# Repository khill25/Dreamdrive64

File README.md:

# DREAMDrive64
Nintendo 64 flash cart based around Raspberry Pi RP2040s. Load roms up to 64MB, EEPROM save support, supports all cic versions.

---
# Getting one
## Buy one from my website! 
https://dreamcraftindustries.com/products/dreamdrive64

## Build your own with PCBWay
You can load up the hw files in Kicad and use the PCBWay plugin. The PCBWay plugin will take you right to the PCBWay website with the gerbers loaded up and ready to order. 

### N64 Cartridge Shell
You can use a doner shell or find some on Aliexpress/Ebay.
The shell will need to be cut to accomodate the SD Card slot and USB port.

* SD Card Slot Cuts 
	* These cuts should be 15mm wide
		* This cut should start approximately 46.5mm from the bottom of the shell on the outside edge.
	* 3mm Deep on the back shell
	* Less than 1mm deep on the front shell
	
* "Boot" Button (Press while plugging in USB to load new firmware)
	* Drill small hole
		* 28.6mm from left side of back shell (5mm right of screw hole)
		* ~6.2mm down from the screw hole

---
# Current Dev Status
* DREAMDrive64 can boot roms and has made the v1.0.0 release! 
	* Menu rom can navigate the sd file system assuming a rational number of files/folders (256 at the moment per directory, 10 directory depth limit)
	* Menu rom can render thumbnail boxart of a rom when scrolling through file list
	* Libdragon changes are needed if you want to compile your own rom for the firmware, those changes are in PR over at the libdragon repo
	* Firmware is stable with a v1.0.0 release available right now, with more improvements on the way.

## Features
| Feature					| Status 	 | Notes 	|
|--------------------------:|:-----------|---------:|
| Rom Loading				| Complete!	 |			|
| SD Filesystem navigation	| Complete!	 | Folder/File limit ~100 per directory 		|
| Wifi						| Soon		 |			|
| EEPROM save support		| Complete!		 |			|
| SRAM support 				| Complete!  | Some games require much higher sram timing than is currently working. SRAM doesn't save to SD card. SRAM data will only persist while the game is running.		|
| CIC Compatibility			| Complete!	 | All cic versions should work. Country version however needs to be matched with the version flashed to the board (PAL vs NTSC) |

**ROM Compatibility **
Still working towards booting at full sdk speeds (0x1240) but current v1.0.0 firmware is at 0x2040. SRAM access isn't fast enough for some titles. 

# Command Registers
| Register					| Address 	 | Length 	| Notes 				|
|--------------------------:|:-----------|:---------|----------------------:|
| Base Address				| 0x1FFE0000 | 0x1000	| 4kB buffer/Currently shared as internal buffer   			| v1/lite and v2|
| Command Interface Start	| 0x1FFE1000 | 0x0800	|						| 
| Random Seed   			| 0x1FFE0008 | 0x4		|						| 
| Start SD Read				| 0x1FFE000C | 0x4		|						| 
| SD Rom Select				| 0x1FFE0010 | 0x4		| Loads selected rom into psram	|
| SD Busy					| 0x1FFE0014 | 0x4  	| After an sd request is sent, data will be available at `Base Address` once sd busy = 0						| v2	|
| SD Read Sector Register 0	| 0x1FFE0018 | 0x4		| High bits of uint64 sector to read	|
| SD Read Sector Register 1	| 0x1FFE001C | 0x4		| Low bits of uin64 sector to read	|
| SD Read number of sectors	| 0x1FFE0020 | 0x4		| v2 code has this hard coded to always read 1 sector	|
| Select Rom				| 0x1FFE0024 | 0xFF		| Send title of rom to load from sd card e.g. "my_homebrew_rom.z64"	|

# Examples of SD card access
There is an open PR for sdfs support in the Libdragon repo! Check that out if you want to patch your libdragon installs.

Libdragon sdfs implementation for DreamDrive64. This code is just snippets and may not "just work" yet. It should give you an idea of how to use the command registers and the order that things need to be done in.
Example code to load a rom with the file's name. Updates to Libdragon's `debug.c` must be made if you plan on using file methods (e.g. f_open, f_read, etc...)
```
// From command register table above
// PC64_CIBASE_ADDRESS_START = "Command Interface start"
// PC64_REGISTER_SD_SELECT_ROM = "Select Rom"
void loadRomAtSelection(char* selectedFile) {
    char* fileToLoad = malloc(sizeof(char*) * 256);
    sprintf(fileToLoad, "%s", selectedFile);

    // Write the file name to the cart buffer
    uint32_t len_aligned32 = (strlen(fileToLoad) + 3) & (-4);
    data_cache_hit_writeback_invalidate(fileToLoad, len_aligned32);
    pi_write_raw(fileToLoad, PC64_BASE_ADDRESS_START, 0, len_aligned32);

    uint32_t sdSelectRomFilenameLength = strlen(fileToLoad);
    io_write(PC64_CIBASE_ADDRESS_START + PC64_REGISTER_SD_SELECT_ROM, sdSelectRomFilenameLength);

    wait_ms(100);
}
```

## Wait for SD
Taken from current (unmerged) libdragon implementation patch
```
static uint8_t pc64_sd_wait() {
    uint32_t timeout = 0;
    uint32_t isBusy __attribute__((aligned(8)));
	isBusy = 1;

    // Wait until the cartridge interface is ready
    do {
		
        // returns 1 while sd card is busy
		isBusy = io_read(PC64_CIBASE_ADDRESS_START + PC64_REGISTER_SD_BUSY);
        
        // Took too long, abort
        if((timeout++) > 10000000) {
			fprintf(stdout, "SD_WAIT timed out. isBusy: %ld\n", isBusy);
			return -1;
		}
    }
    while(isBusy != 0);
    (void) timeout; // Needed to stop unused variable warning

    // Success
    return 0;
}
```

## Read
Taken from current (unmerged) libdragon implementation patch
```
static DRESULT fat_disk_read_pc64(BYTE* buff, LBA_t sector, UINT count) {
	_Static_assert(FF_MIN_SS == 512, "this function assumes sector size == 512");
	_Static_assert(FF_MAX_SS == 512, "this function assumes sector size == 512");

	int retryCount = 2;
	int i = 0;
	do {
		uint64_t current_sector = sector + i;
		
		uint32_t part0 __attribute__((aligned(8)));
		part0 = (current_sector & 0xFFFFFFFF00000000LL) >> 32;

		uint32_t part1 __attribute__((aligned(8)));
		part1 = (current_sector & 0x00000000FFFFFFFFLL);

		// send sector
		io_write(PC64_CIBASE_ADDRESS_START + PC64_REGISTER_SD_READ_SECTOR0, part0);

		io_write(PC64_CIBASE_ADDRESS_START + PC64_REGISTER_SD_READ_SECTOR1, part1);

		// send num sectors to read
		io_write(PC64_CIBASE_ADDRESS_START + PC64_REGISTER_SD_READ_NUM_SECTORS, 1);

		// start the load
		io_write(PC64_CIBASE_ADDRESS_START + PC64_COMMAND_SD_READ, 1);

        // wait for the sd card to finish
        if(pc64_sd_wait() == 0) {
			data_cache_hit_writeback_invalidate(buff, 512);
			dma_read(buff, PC64_BASE_ADDRESS_START, 512);
			buff += 512;
			i++;
		} else {
			retryCount--;
			fprintf(stderr, "wait timeout\n");
		}

		if (retryCount <= 0) {
			break;
		}
		
	} while (i < count);

	return RES_OK;
}
```

## Write
Not supported yet!

# Join in on the fun!
Dreamcraft Industries discord

[Join the Dreamcraft Discord!](https://discord.gg/yawWMcv6tC)

Original PicoCart64 discord
Join the Discord server to participate in the discussion and development of this project.
[Dubious Technology Discord](https://discord.gg/2Gb3jWqqja)

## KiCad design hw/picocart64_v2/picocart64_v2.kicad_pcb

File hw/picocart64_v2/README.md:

# PicoCart64 v2.2

:exclamation: Latest 2.2 board revisions have been ordered for testing, so build at your own risk :exclamation:

## Errata

### v2.0
- Less than ideal VBus' routing on Inner Layer 1. The power routing should work and passes DRC, but could be better.

## Changelog

### v2.2
- Improved routing
- Removed mcu1 USB-C port
- CS line of all chips in PSRAM array are routed through the demux
- Removed play area
- Added reset button pads connected to mcu2 reset pins for easy reset

### v2.1-unreleased
- Improved power routing for VBus'

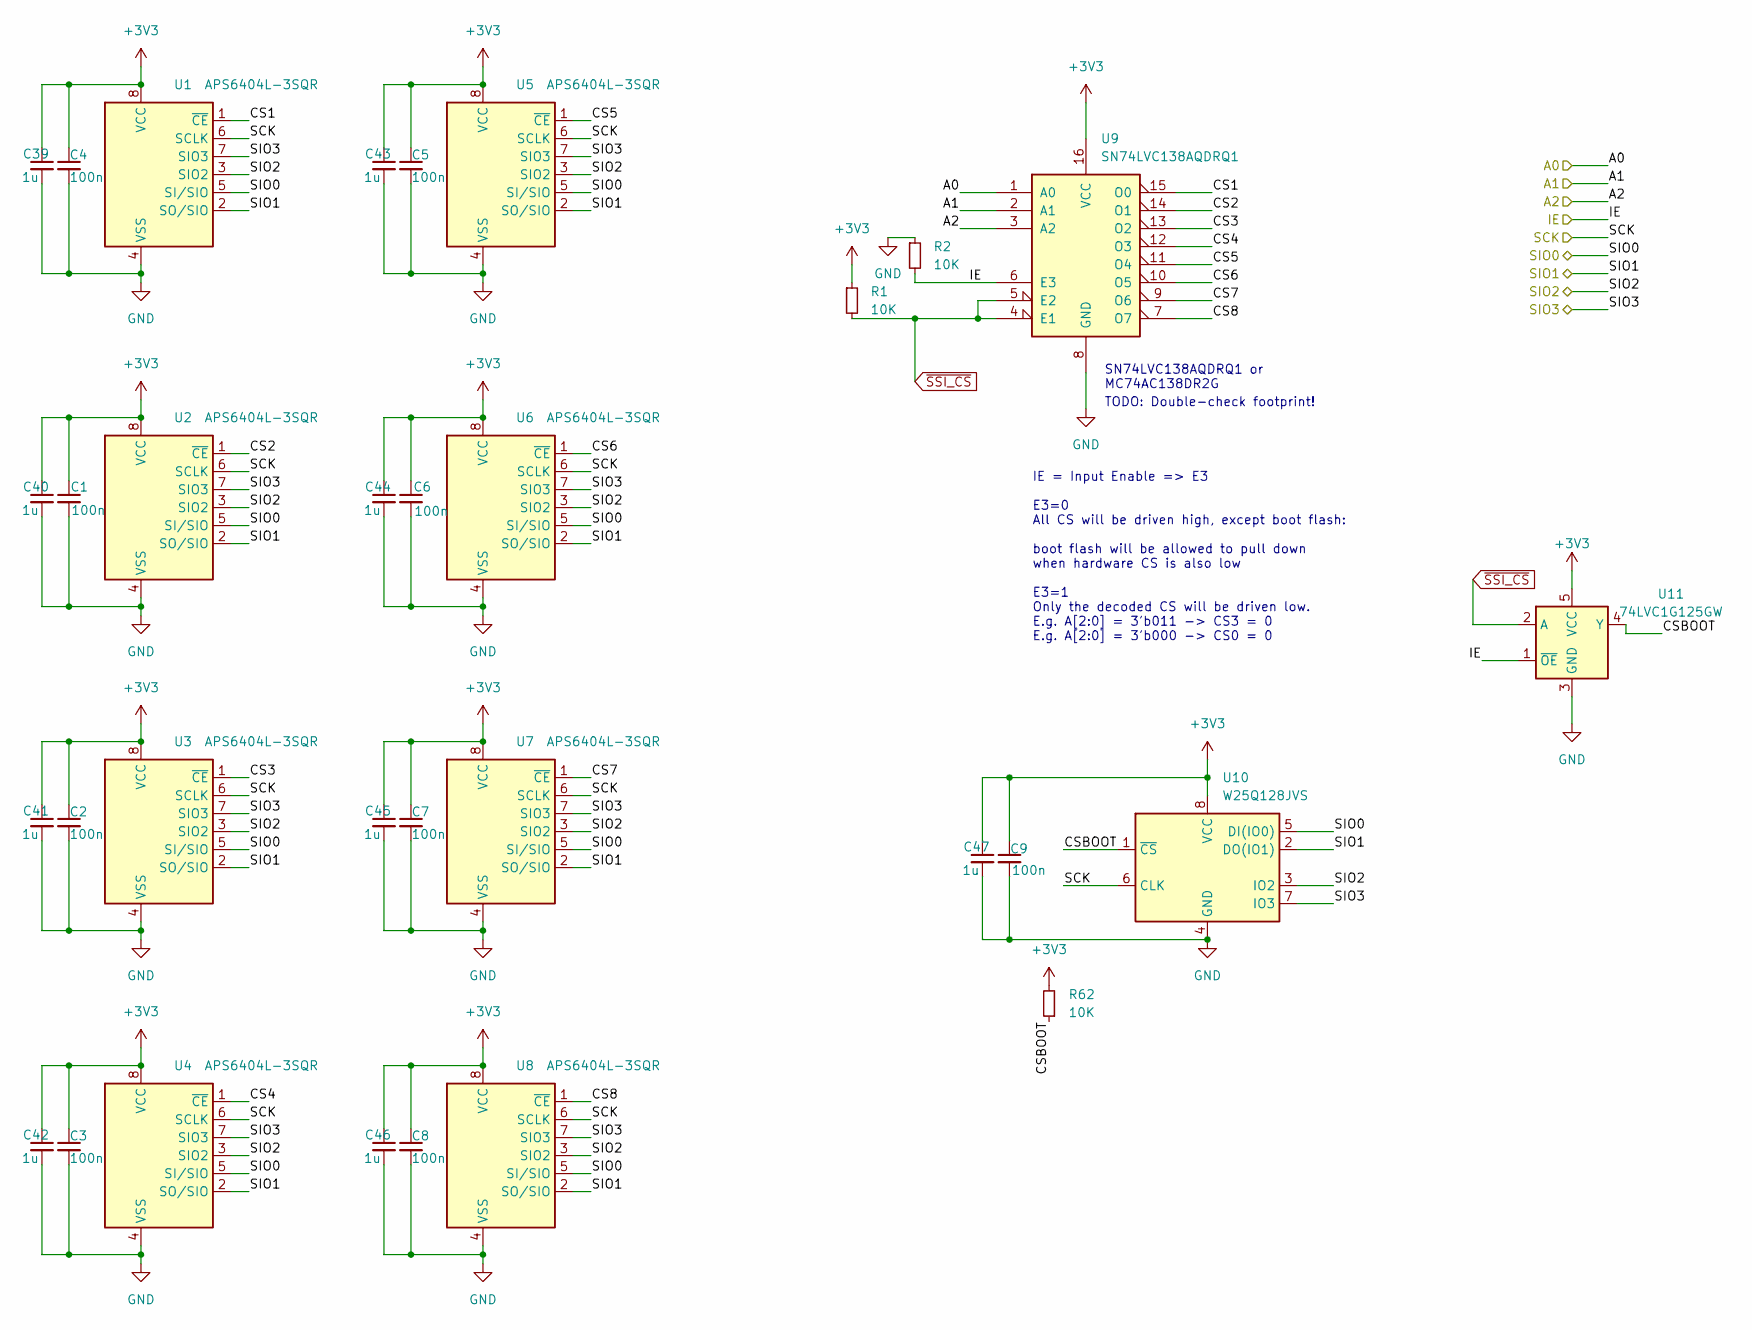
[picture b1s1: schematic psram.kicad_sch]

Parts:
C1, C2, C3, C4, C5, C6, C7, C8, C9: 100n; C_0402_1005Metric; LCSC C1525
C39, C40, C41, C42, C43, C44, C45, C46, C47: 1u; C_0402_1005Metric; LCSC C14445
R1, R2, R62: 10K; R_0402_1005Metric; LCSC C406733
U1, U2, U3, U4, U5, U6, U7, U8: APS6404L-3SQR; SOP-8_3.76x4.96mm_P1.27mm; LCSC Mouser: APS6404L-3SQR-SN
U9: SN74LVC138AQDRQ1; SOP-16_4.4x10.4mm_P1.27mm; LCSC C7816
U10: W25Q128JVS; SOIC-8_5.23x5.23mm_P1.27mm; LCSC C97521
U11: 74LVC1G125GW; SOT-353_SC-70-5; LCSC C12519

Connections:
+3V3: C1.1, C2.1, C3.1, C4.1, C5.1, C6.1, C7.1, C8.1, C9.1, C39.1, C40.1, C41.1, C42.1, C43.1, C44.1, C45.1, C46.1, C47.1, R1.1, R62.2, U1.8 (VCC), U2.8 (VCC), U3.8 (VCC), U4.8 (VCC), U5.8 (VCC), U6.8 (VCC), U7.8 (VCC), U8.8 (VCC), U9.16 (VCC), U10.8 (VCC), U11.5 (VCC); also elsewhere on the board
/Mainboard/DEMUX_A0: U9.1 (A0); also elsewhere on the board
/Mainboard/DEMUX_A1: U9.2 (A1); also elsewhere on the board
/Mainboard/DEMUX_A2: U9.3 (A2); also elsewhere on the board
/Mainboard/DEMUX_IE: R2.2, U9.6 (E3), U11.1 (~OE); also elsewhere on the board
/Mainboard/SSI_SCLK: U1.6 (SCLK), U2.6 (SCLK), U3.6 (SCLK), U4.6 (SCLK), U5.6 (SCLK), U6.6 (SCLK), U7.6 (SCLK), U8.6 (SCLK), U10.6 (CLK); also elsewhere on the board
/Mainboard/SSI_SD0: U1.5 (SI/SIO), U2.5 (SI/SIO), U3.5 (SI/SIO), U4.5 (SI/SIO), U5.5 (SI/SIO), U6.5 (SI/SIO), U7.5 (SI/SIO), U8.5 (SI/SIO), U10.5 (DI(IO0)); also elsewhere on the board
/Mainboard/SSI_SD1: U1.2 (SO/SIO), U2.2 (SO/SIO), U3.2 (SO/SIO), U4.2 (SO/SIO), U5.2 (SO/SIO), U6.2 (SO/SIO), U7.2 (SO/SIO), U8.2 (SO/SIO), U10.2 (DO(IO1)); also elsewhere on the board
/Mainboard/SSI_SD2: U1.3 (SIO2), U2.3 (SIO2), U3.3 (SIO2), U4.3 (SIO2), U5.3 (SIO2), U6.3 (SIO2), U7.3 (SIO2), U8.3 (SIO2), U10.3 (IO2); also elsewhere on the board
/Mainboard/SSI_SD3: U1.7 (SIO3), U2.7 (SIO3), U3.7 (SIO3), U4.7 (SIO3), U5.7 (SIO3), U6.7 (SIO3), U7.7 (SIO3), U8.7 (SIO3), U10.7 (IO3); also elsewhere on the board
/PSRAM Array/CS1: U1.1 (~CE), U9.15 (O0)
/PSRAM Array/CS2: U2.1 (~CE), U9.14 (O1)
/PSRAM Array/CS3: U3.1 (~CE), U9.13 (O2)
/PSRAM Array/CS4: U4.1 (~CE), U9.12 (O3)
/PSRAM Array/CS5: U5.1 (~CE), U9.11 (O4)
/PSRAM Array/CS6: U6.1 (~CE), U9.10 (O5)
/PSRAM Array/CS7: U7.1 (~CE), U9.9 (O6)
/PSRAM Array/CS8: U8.1 (~CE), U9.7 (O7)
/PSRAM Array/CSBOOT: R62.1, U10.1 (~CS), U11.4 (Y)
GND: C1.2, C2.2, C3.2, C4.2, C5.2, C6.2, C7.2, C8.2, C9.2, C39.2, C40.2, C41.2, C42.2, C43.2, C44.2, C45.2, C46.2, C47.2, R2.1, U1.4 (VSS), U2.4 (VSS), U3.4 (VSS), U4.4 (VSS), U5.4 (VSS), U6.4 (VSS), U7.4 (VSS), U8.4 (VSS), U9.8 (GND), U10.4 (GND), U11.3 (GND); also elsewhere on the board
~SSI_CS: R1.2, U9.4 (E1), U9.5 (E2), U11.2 (A); also elsewhere on the board

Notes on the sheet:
TODO: Double-check footprint!
IE = Input Enable => E3 E3=0 All CS will be driven high, except boot flash: boot flash will be allowed to pull down when hardware CS is also low E3=1 Only the decoded CS will be driven low. E.g. A[2:0] = 3'b011 -> CS3 = 0 E.g. A[2:0] = 3'b000 -> CS0 = 0
SN74LVC138AQDRQ1 or MC74AC138DR2G

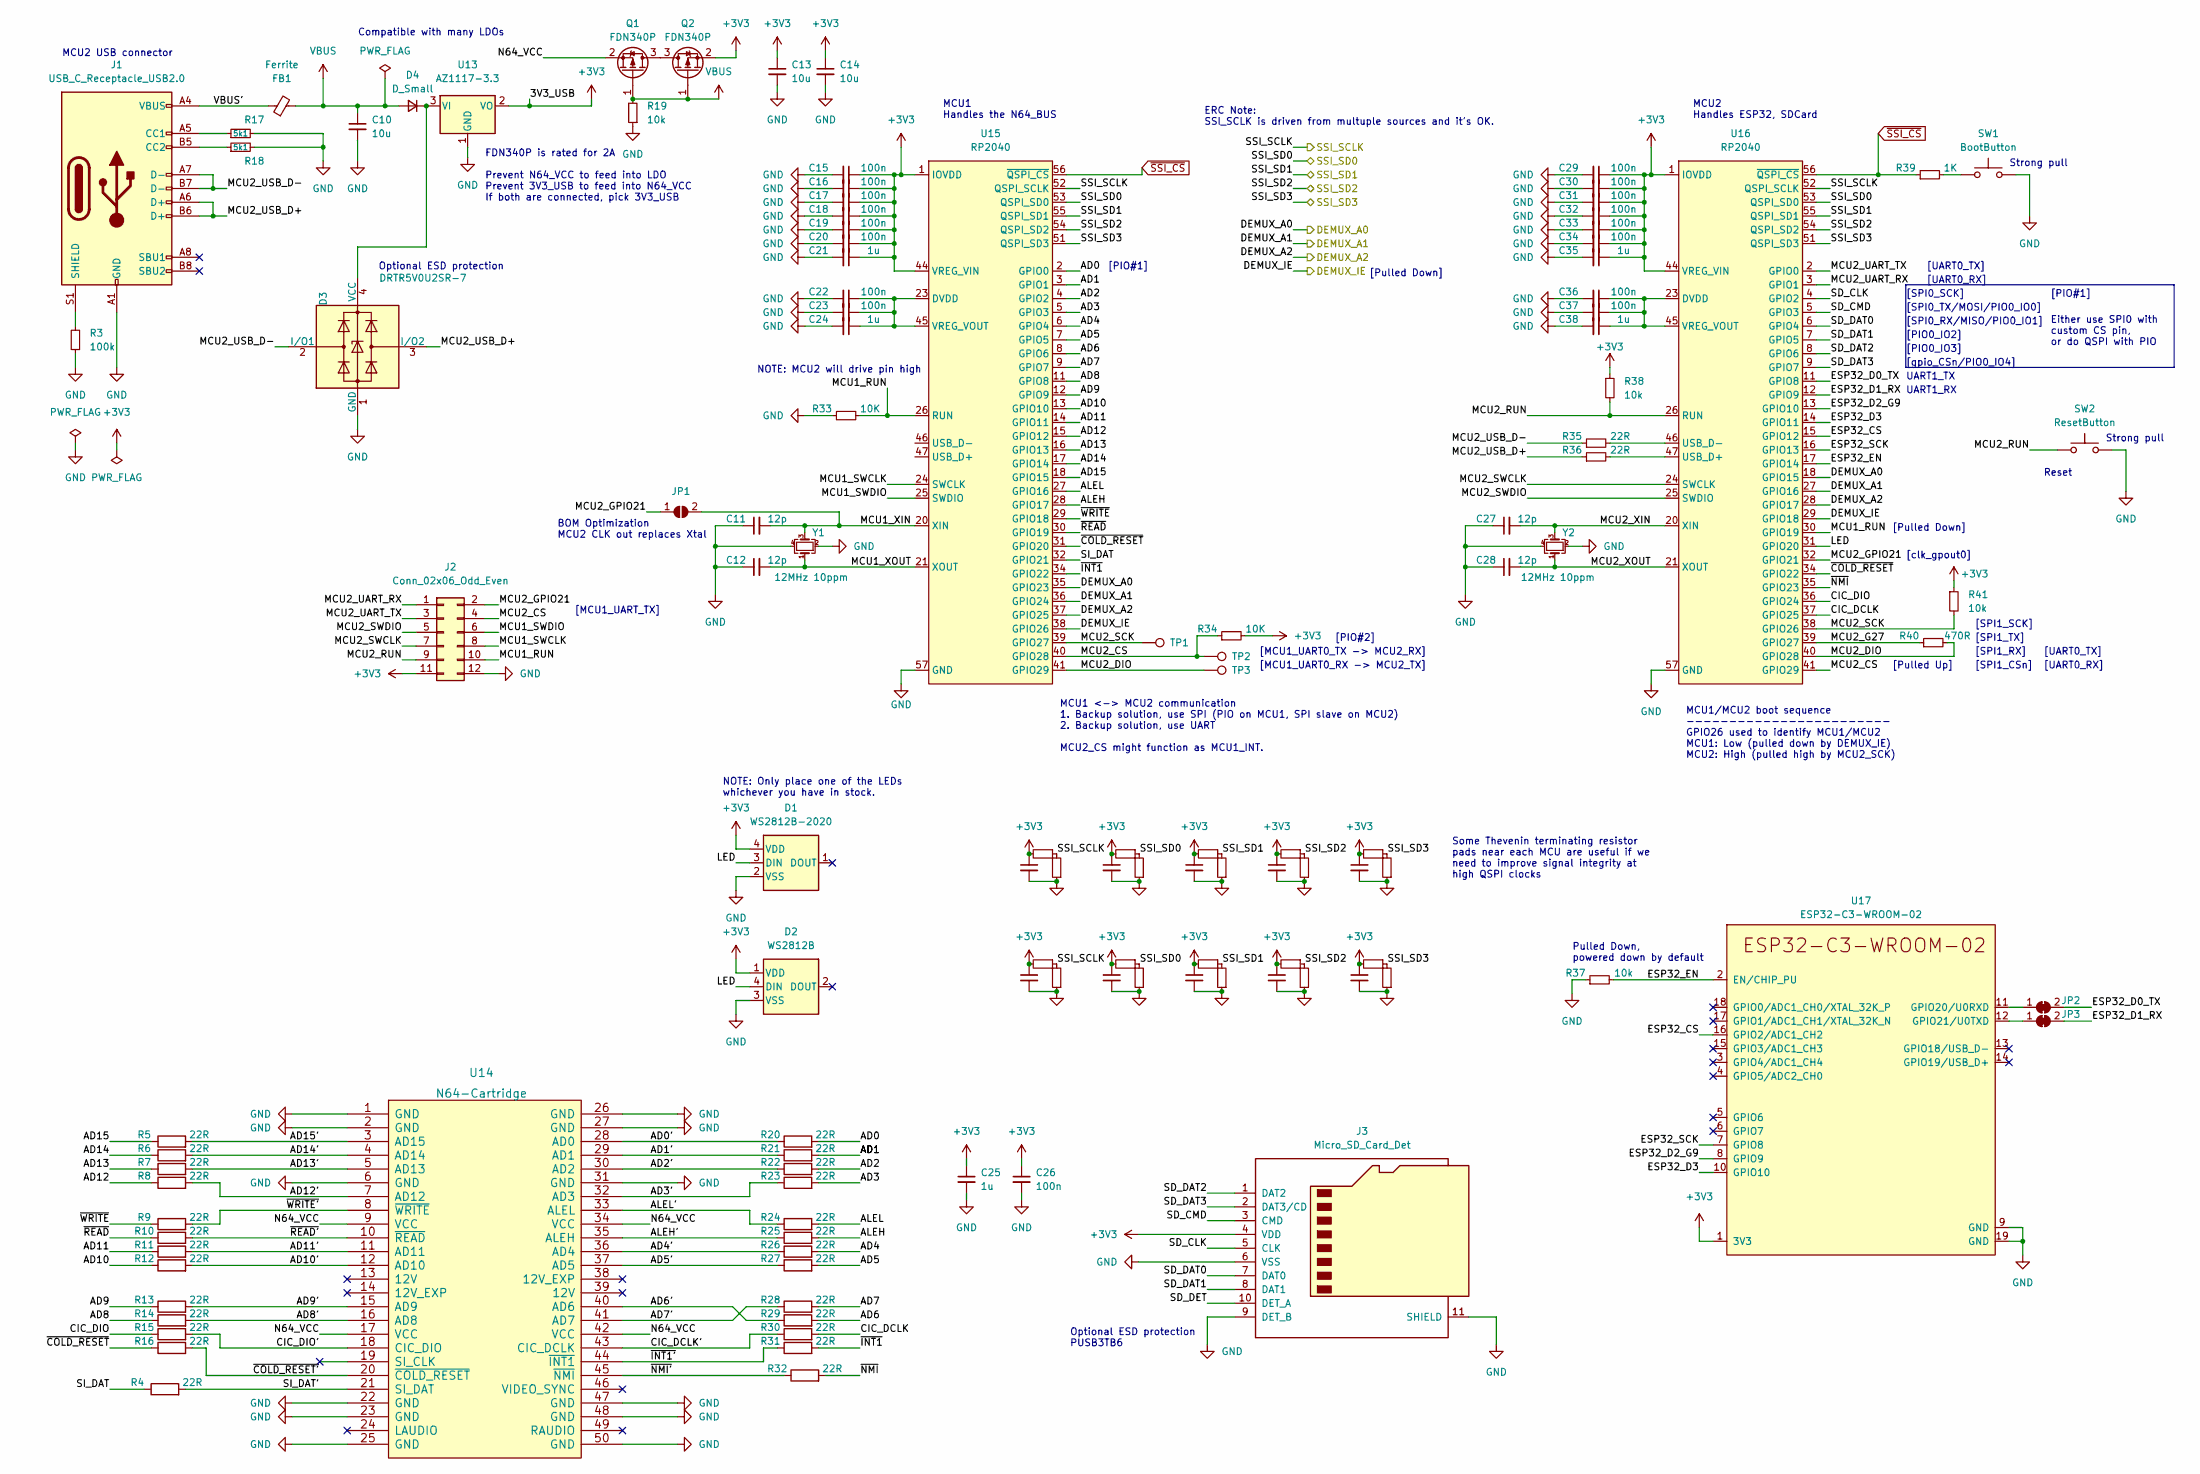
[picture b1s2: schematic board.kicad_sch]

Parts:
C10, C13, C14: 10u; C_0603_1608Metric; LCSC C15525
C11, C12, C27, C28: 12p; C_0402_1005Metric; LCSC C106201
C15, C16, C17, C18, C19, C20, C22, C23, C26, C29, C30, C31, C32, C33, C34, C36, C37, C48, C49, C50, C51, C52, C53, C54, C55, C56, C57: 100n; C_0402_1005Metric; LCSC C1525
C21, C24, C25, C35, C38: 1u; C_0402_1005Metric; LCSC C14445
D1: WS2812B-2020; LCSC C965555
D2: WS2812B; LED_WS2812B_PLCC4_5.0x5.0mm_P3.2mm; LCSC C114586
D3: DRTR5V0U2SR-7; SOT-143; LCSC C443828
D4: D_Small; D_SMA; LCSC C22452
FB1: Ferrite; L_0603_1608Metric; LCSC C76892
J1: USB_C_Receptacle_USB2.0; USB_C_Receptacle_GT-USB-7010; LCSC C136423
J2: Conn_02x06_Odd_Even; PinHeader_2x06_P2.54mm_Vertical_SMD
J3: Micro_SD_Card_Det; microSD_HC_Molex_104031-0811; LCSC C585350
JP1: SolderJumper_2_Open; SolderJumper-2_Small_Open
JP2, JP3: SolderJumper_2_Bridged; SolderJumper-2_Small_Closed
Q1, Q2: FDN340P; SOT-23; LCSC C347510
R3: 100k; R_0402_1005Metric; LCSC C25741
R4, R5, R6, R7, R8, R9, R10, R11, R12, R13, R14, R15, R16, R20, R21, R22, R23, R24, R25, R26, R27, R28, R29, R30, R31, R32, R35, R36: 22R; R_0402_1005Metric; LCSC C409710
R17, R18: 5k1; R_0402_1005Metric; LCSC C105873
R19, R37, R38, R41: 10k; R_0402_1005Metric; LCSC C406733
R33, R34: 10K; R_0402_1005Metric; LCSC C406733
R39, R42, R43, R44, R45, R46, R47, R48, R49, R50, R51, R52, R53, R54, R55, R56, R57, R58, R59, R60, R61: 1K; R_0402_1005Metric; LCSC C105637
R40: 470R; R_0402_1005Metric; LCSC C25117
SW1: BootButton; SW_SPST_FSMSM; LCSC C318938
SW2: ResetButton; SW_SPST_FSMSM; LCSC C318938
TP1: TP_MCU2_SCK; TestPoint_Pad_D1.0mm
TP2: TP_MCU2_CS; TestPoint_Pad_D1.0mm
TP3: TP_MCU2_DIO; TestPoint_Pad_D1.0mm
U13: AZ1117-3.3; SOT-223; LCSC C108495
U14: N64-Cartridge; N64-Connector
U15, U16: RP2040; QFN-56_EP_7x7_Pitch0.4mm; LCSC C2040
U17: ESP32-C3-WROOM-02; LCSC C2934560
Y1, Y2: 12MHz 10ppm; Crystal_SMD_2520-4Pin_2.5x2.0mm; LCSC C521567

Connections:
+3V3: C13.1, C14.1, C15.1, C16.1, C17.1, C18.1, C19.1, C20.1, C21.1, C25.1, C26.1, C29.1, C30.1, C31.1, C32.1, C33.1, C34.1, C35.1, C48.1, C49.1, C50.1, C51.1, C52.1, C53.1, C54.1, C55.1, C56.1, C57.1, D1.4 (VDD), D2.1 (VDD), J2.11, J3.4 (VDD), Q2.2 (S), R34.2, R38.1, R41.1, R42.2, R43.2, R46.2, R47.2, R50.2, R51.2, R54.2, R55.2, R58.2, R59.2, U13.2 (VO), U15.1 (IOVDD), U15.10 (IOVDD), U15.22 (IOVDD), U15.33 (IOVDD), U15.42 (IOVDD), U15.43 (ADC_AVDD), U15.44 (VREG_VIN), U15.48 (USB_VDD), U15.49 (IOVDD), U16.1 (IOVDD), U16.10 (IOVDD), U16.22 (IOVDD), U16.33 (IOVDD), U16.42 (IOVDD), U16.43 (ADC_AVDD), U16.44 (VREG_VIN), U16.48 (USB_VDD), U16.49 (IOVDD), U17.1 (3V3); also elsewhere on the board
/Mainboard/AD0: R20.2, U15.2 (GPIO0)
/Mainboard/AD0': R20.1, U14.28 (AD0)
/Mainboard/AD1: R21.2, U15.3 (GPIO1)
/Mainboard/AD1': R21.1, U14.29 (AD1)
/Mainboard/AD2: R22.2, U15.4 (GPIO2)
/Mainboard/AD2': R22.1, U14.30 (AD2)
/Mainboard/AD3: R23.2, U15.5 (GPIO3)
/Mainboard/AD3': R23.1, U14.32 (AD3)
/Mainboard/AD4: R26.2, U15.6 (GPIO4)
/Mainboard/AD4': R26.1, U14.36 (AD4)
/Mainboard/AD5: R27.2, U15.7 (GPIO5)
/Mainboard/AD5': R27.1, U14.37 (AD5)
/Mainboard/AD6: R29.2, U15.8 (GPIO6)
/Mainboard/AD6': R29.1, U14.40 (AD6)
/Mainboard/AD7: R28.2, U15.9 (GPIO7)
/Mainboard/AD7': R28.1, U14.41 (AD7)
/Mainboard/AD8: R14.1, U15.11 (GPIO8)
/Mainboard/AD8': R14.2, U14.16 (AD8)
/Mainboard/AD9: R13.1, U15.12 (GPIO9)
/Mainboard/AD9': R13.2, U14.15 (AD9)
/Mainboard/AD10: R12.1, U15.13 (GPIO10)
/Mainboard/AD10': R12.2, U14.12 (AD10)
/Mainboard/AD11: R11.1, U15.14 (GPIO11)
/Mainboard/AD11': R11.2, U14.11 (AD11)
/Mainboard/AD12: R8.1, U15.15 (GPIO12)
/Mainboard/AD12': R8.2, U14.7 (AD12)
/Mainboard/AD13: R7.1, U15.16 (GPIO13)
/Mainboard/AD13': R7.2, U14.5 (AD13)
/Mainboard/AD14: R6.1, U15.17 (GPIO14)
/Mainboard/AD14': R6.2, U14.4 (AD14)
/Mainboard/AD15: R5.1, U15.18 (GPIO15)
/Mainboard/AD15': R5.2, U14.3 (AD15)
/Mainboard/ALEH: R25.2, U15.28 (GPIO17)
/Mainboard/ALEH': R25.1, U14.35 (ALEH)
/Mainboard/ALEL: R24.2, U15.27 (GPIO16)
/Mainboard/ALEL': R24.1, U14.33 (ALEL)
/Mainboard/CIC_DCLK: R30.2, U16.37 (GPIO25)
/Mainboard/CIC_DCLK': R30.1, U14.43 (CIC_DCLK)
/Mainboard/CIC_DIO: R15.1, U16.36 (GPIO24)
/Mainboard/CIC_DIO': R15.2, U14.18 (CIC_DIO)
/Mainboard/DEMUX_A0: U15.35 (GPIO23), U16.18 (GPIO15); also elsewhere on the board
/Mainboard/DEMUX_A1: U15.36 (GPIO24), U16.27 (GPIO16); also elsewhere on the board
/Mainboard/DEMUX_A2: U15.37 (GPIO25), U16.28 (GPIO17); also elsewhere on the board
/Mainboard/DEMUX_IE: U15.38 (GPIO26), U16.29 (GPIO18); also elsewhere on the board
/Mainboard/ESP32_CS: U16.15 (GPIO12), U17.16 (GPIO2/ADC1_CH2)
/Mainboard/ESP32_D0_TX: JP2.2 (B), U16.11 (GPIO8)
/Mainboard/ESP32_D1_RX: JP3.2 (B), U16.12 (GPIO9)
/Mainboard/ESP32_D2_G9: U16.13 (GPIO10), U17.8 (GPIO9)
/Mainboard/ESP32_D3: U16.14 (GPIO11), U17.10 (GPIO10)
/Mainboard/ESP32_EN: R37.2, U16.17 (GPIO14), U17.2 (EN/CHIP_PU)
/Mainboard/ESP32_SCK: U16.16 (GPIO13), U17.7 (GPIO8)
/Mainboard/LED: D1.3 (DIN), D2.4 (DIN), U16.31 (GPIO20)
/Mainboard/MCU1_RUN: J2.10, R33.2, U15.26 (RUN), U16.30 (GPIO19)
/Mainboard/MCU1_SWCLK: J2.8, U15.24 (SWCLK)
/Mainboard/MCU1_SWDIO: J2.6, U15.25 (SWDIO)
/Mainboard/MCU1_XIN: C11.2, JP1.2 (B), U15.20 (XIN), Y1.3
/Mainboard/MCU1_XOUT: C12.2, U15.21 (XOUT), Y1.1
/Mainboard/MCU2_CS: J2.4, R34.1, TP2.1, U15.40 (GPIO28), U16.41 (GPIO29)
/Mainboard/MCU2_DIO: R40.2, TP3.1, U15.41 (GPIO29), U16.40 (GPIO28)
/Mainboard/MCU2_G27: R40.1, U16.39 (GPIO27)
/Mainboard/MCU2_GPIO21: J2.2, JP1.1 (A), U16.32 (GPIO21)
/Mainboard/MCU2_RUN: J2.9, R38.2, SW2.1, U16.26 (RUN)
/Mainboard/MCU2_SCK: R41.2, TP1.1, U15.39 (GPIO27), U16.38 (GPIO26)
/Mainboard/MCU2_SWCLK: J2.7, U16.24 (SWCLK)
/Mainboard/MCU2_SWDIO: J2.5, U16.25 (SWDIO)
/Mainboard/MCU2_UART_RX: J2.1, U16.3 (GPIO1)
/Mainboard/MCU2_UART_TX: J2.3, U16.2 (GPIO0)
/Mainboard/MCU2_USB_D+: D3.3 (I/O2), J1.A6 (D+), J1.B6 (D+), R36.1
/Mainboard/MCU2_USB_D-: D3.2 (I/O1), J1.A7 (D-), J1.B7 (D-), R35.1
/Mainboard/MCU2_XIN: C27.2, U16.20 (XIN), Y2.3
/Mainboard/MCU2_XOUT: C28.2, U16.21 (XOUT), Y2.1
/Mainboard/N64_VCC: Q1.2 (S), U14.9 (VCC), U14.17 (VCC), U14.34 (VCC), U14.42 (VCC)
/Mainboard/SD_CLK: J3.5 (CLK), U16.4 (GPIO2)
/Mainboard/SD_CMD: J3.3 (CMD), U16.5 (GPIO3)
/Mainboard/SD_DAT0: J3.7 (DAT0), U16.6 (GPIO4)
/Mainboard/SD_DAT1: J3.8 (DAT1), U16.7 (GPIO5)
/Mainboard/SD_DAT2: J3.1 (DAT2), U16.8 (GPIO6)
/Mainboard/SD_DAT3: J3.2 (DAT3/CD), U16.9 (GPIO7)
/Mainboard/SD_DET: J3.10 (DET_A)
/Mainboard/SI_DAT: R4.1, U15.32 (GPIO21)
/Mainboard/SI_DAT': R4.2, U14.21 (SI_DAT)
/Mainboard/SSI_SCLK: R42.1, R43.1, R44.2, R45.2, U15.52 (QSPI_SCLK), U16.52 (QSPI_SCLK); also elsewhere on the board
/Mainboard/SSI_SD0: R46.1, R47.1, R48.2, R49.2, U15.53 (QSPI_SD0), U16.53 (QSPI_SD0); also elsewhere on the board
/Mainboard/SSI_SD1: R50.1, R51.1, R52.2, R53.2, U15.55 (QSPI_SD1), U16.55 (QSPI_SD1); also elsewhere on the board
/Mainboard/SSI_SD2: R54.1, R55.1, R56.2, R57.2, U15.54 (QSPI_SD2), U16.54 (QSPI_SD2); also elsewhere on the board
/Mainboard/SSI_SD3: R58.1, R59.1, R60.2, R61.2, U15.51 (QSPI_SD3), U16.51 (QSPI_SD3); also elsewhere on the board
/Mainboard/VBUS': FB1.1, J1.A4 (VBUS), J1.A9 (VBUS), J1.B4 (VBUS), J1.B9 (VBUS)
/Mainboard/~COLD_RESET': R16.2, U14.20 (~COLD_RESET)
/Mainboard/~COLD_RESET: R16.1, U15.31 (GPIO20), U16.34 (GPIO22)
/Mainboard/~INT1': R31.1, U14.44 (~INT1)
/Mainboard/~INT1: R31.2, U15.34 (GPIO22)
/Mainboard/~NMI': R32.1, U14.45 (~NMI)
/Mainboard/~NMI: R32.2, U16.35 (GPIO23)
/Mainboard/~READ': R10.2, U14.10 (~READ)
/Mainboard/~READ: R10.1, U15.30 (GPIO19)
/Mainboard/~WRITE': R9.2, U14.8 (~WRITE)
/Mainboard/~WRITE: R9.1, U15.29 (GPIO18)
GND: C10.2, C11.1, C12.1, C13.2, C14.2, C15.2, C16.2, C17.2, C18.2, C19.2, C20.2, C21.2, C22.2, C23.2, C24.2, C25.2, C26.2, C27.1, C28.1, C29.2, C30.2, C31.2, C32.2, C33.2, C34.2, C35.2, C36.2, C37.2, C38.2, C48.2, C49.2, C50.2, C51.2, C52.2, C53.2, C54.2, C55.2, C56.2, C57.2, D1.2 (VSS), D2.3 (VSS), D3.1 (GND), J1.A1 (GND), J1.A12 (GND), J1.B1 (GND), J1.B12 (GND), J2.12, J3.6 (VSS), J3.9 (DET_B), J3.11 (SHIELD), R3.1, R17.2, R18.2, R19.1, R33.1, R37.1, R44.1, R45.1, R48.1, R49.1, R52.1, R53.1, R56.1, R57.1, R60.1, R61.1, SW1.2, SW2.2, U13.1 (GND), U14.1 (GND), U14.2 (GND), U14.6 (GND), U14.22 (GND), U14.23 (GND), U14.25 (GND), U14.26 (GND), U14.27 (GND), U14.31 (GND), U14.47 (GND), U14.48 (GND), U14.50 (GND), U15.19 (TESTEN), U15.57 (GND), U16.19 (TESTEN), U16.57 (GND), U17.9 (GND), U17.19 (GND), Y1.2, Y1.4, Y2.2, Y2.4; also elsewhere on the board
unnamed: C22.1, C23.1, C24.1, U15.23 (DVDD), U15.45 (VREG_VOUT), U15.50 (DVDD)
unnamed: C36.1, C37.1, C38.1, U16.23 (DVDD), U16.45 (VREG_VOUT), U16.50 (DVDD)
unnamed: D3.4 (VCC), D4.1 (K), U13.3 (VI)
unnamed: J1.A5 (CC1), R17.1
unnamed: J1.B5 (CC2), R18.1
unnamed: J1.S1 (SHIELD), R3.2
unnamed: JP2.1 (A), U17.11 (GPIO20/U0RXD)
unnamed: JP3.1 (A), U17.12 (GPIO21/U0TXD)
unnamed: Q1.3 (D), Q2.3 (D)
unnamed: R35.2, U16.46 (USB_D-)
unnamed: R36.2, U16.47 (USB_D+)
unnamed: R39.2, SW1.1
VBUS: C10.1, D4.2 (A), FB1.2, Q1.1 (G), Q2.1 (G), R19.2
~SSI_CS: R39.1, U15.56 (~QSPI_CS), U16.56 (~QSPI_CS); also elsewhere on the board

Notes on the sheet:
[UART0_TX]
[PIO0_IO2]
[Pulled Up]
[clk_gpout0]
UART1_TX
[MCU1_UART0_RX -> MCU2_TX]
NOTE: MCU2 will drive pin high
[Pulled Down]
Strong pull
[UART0_RX]
MCU2 Handles ESP32, SDCard
FDN340P is rated for 2A Prevent N64_VCC to feed into LDO Prevent 3V3_USB to feed into N64_VCC If both are connected, pick 3V3_USB
Optional ESD protection PUSB3TB6
NOTE: Only place one of the LEDs whichever you have in stock.
[PIO#1]
Compatible with many LDOs
UART1_RX
BOM Optimization MCU2 CLK out replaces Xtal
Some Thevenin terminating resistor pads near each MCU are useful if we need to improve signal integrity at high QSPI clocks
[SPI1_SCK]
[SPI0_TX/MOSI/PIO0_IO0]
MCU1/MCU2 boot sequence ------------------------ GPIO26 used to identify MCU1/MCU2 MCU1: Low (pulled down by DEMUX_IE) MCU2: High (pulled high by MCU2_SCK)
[SPI0_SCK]
Either use SPI0 with custom CS pin, or do QSPI with PIO
[MCU1_UART_TX]
[SPI1_TX]
[MCU1_UART0_TX -> MCU2_RX]
[SPI1_RX]
ERC Note: SSI_SCLK is driven from multuple sources and it's OK.
MCU2 USB connector
[PIO0_IO3]
[PIO#2]
Optional ESD protection
MCU1 <-> MCU2 communication 1. Backup solution, use SPI (PIO on MCU1, SPI slave on MCU2) 2. Backup solution, use UART MCU2_CS might function as MCU1_INT.
Reset
[SPI0_RX/MISO/PIO0_IO1]
Pulled Down, powered down by default
MCU1 Handles the N64_BUS
[gpio_CSn/PIO0_IO4]
[SPI1_CSn]

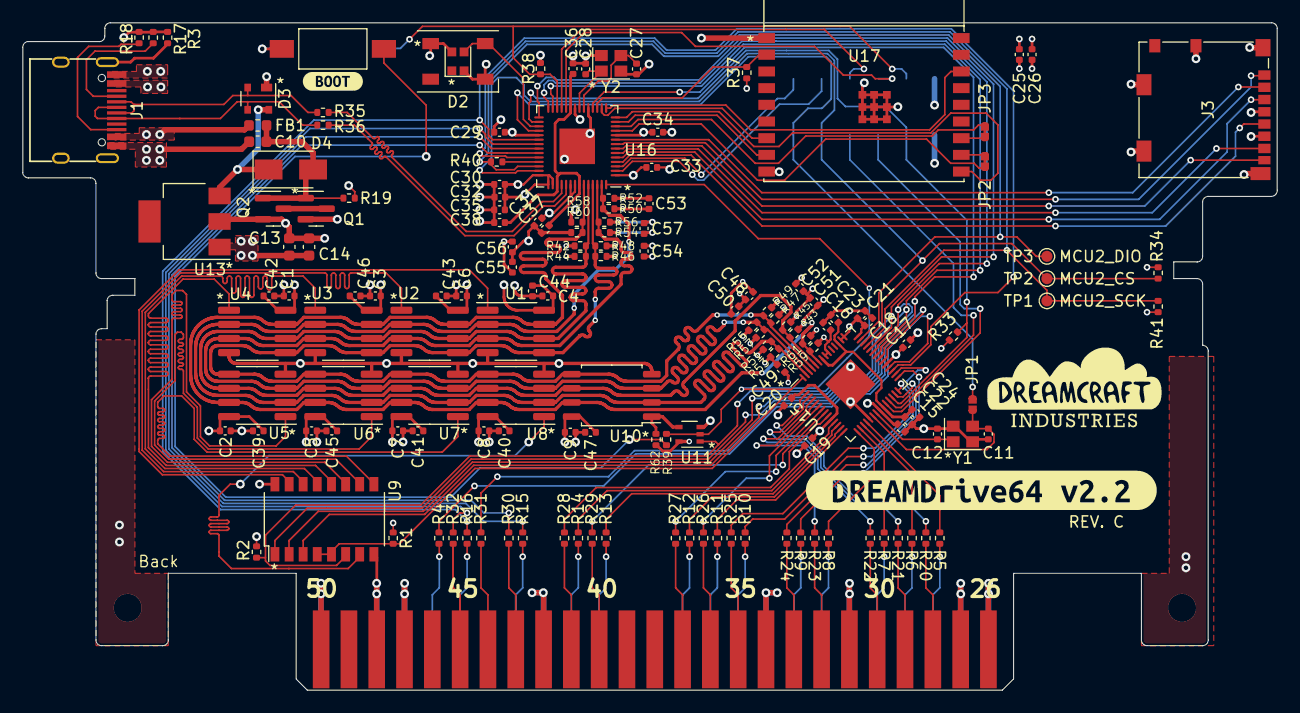
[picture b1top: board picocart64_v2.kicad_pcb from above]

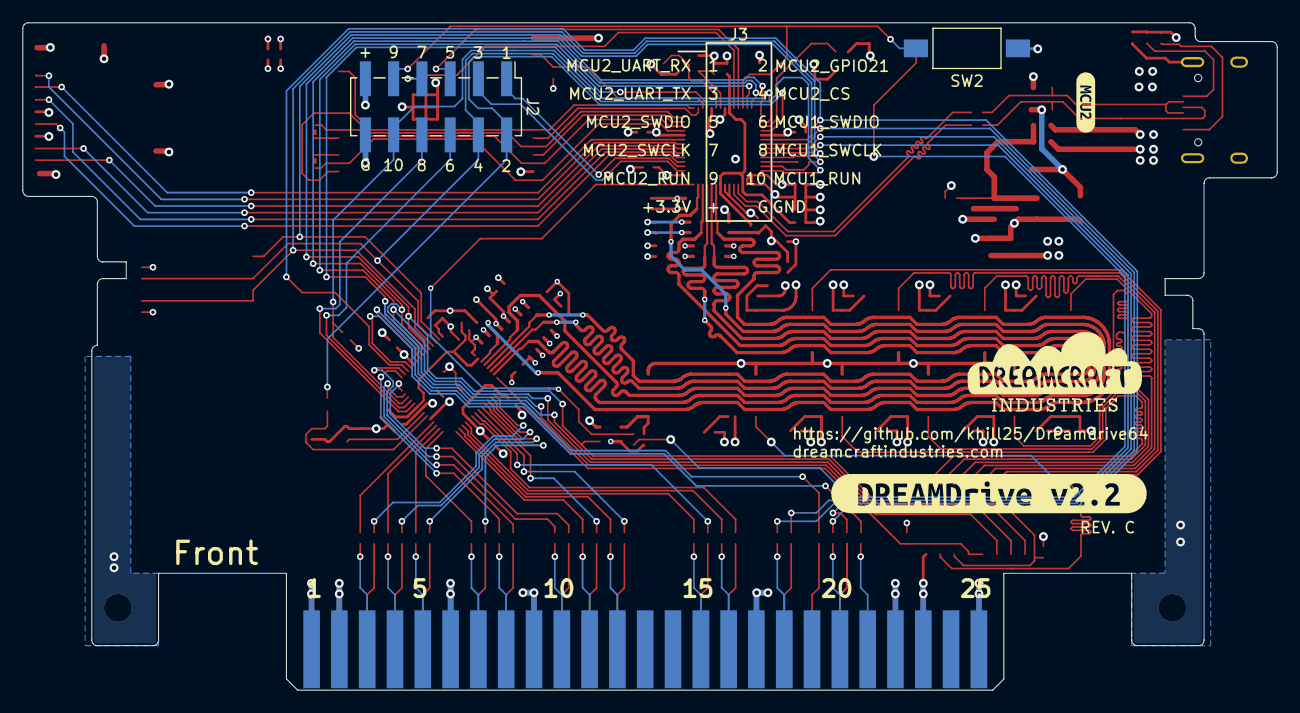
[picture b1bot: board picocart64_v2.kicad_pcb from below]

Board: 4 copper layers, 112.8 x 60.0 mm, 159 parts (5 on the bottom side), 121 nets.

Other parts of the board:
kibuzzard-62F8E97D: G***; kibuzzard-62F8E97D
kibuzzard-62F95F09: G***; kibuzzard-62F95F09
kibuzzard-63B14A32: G***; kibuzzard-63B14A32
kibuzzard-63B14B13: G***; kibuzzard-63B14B13

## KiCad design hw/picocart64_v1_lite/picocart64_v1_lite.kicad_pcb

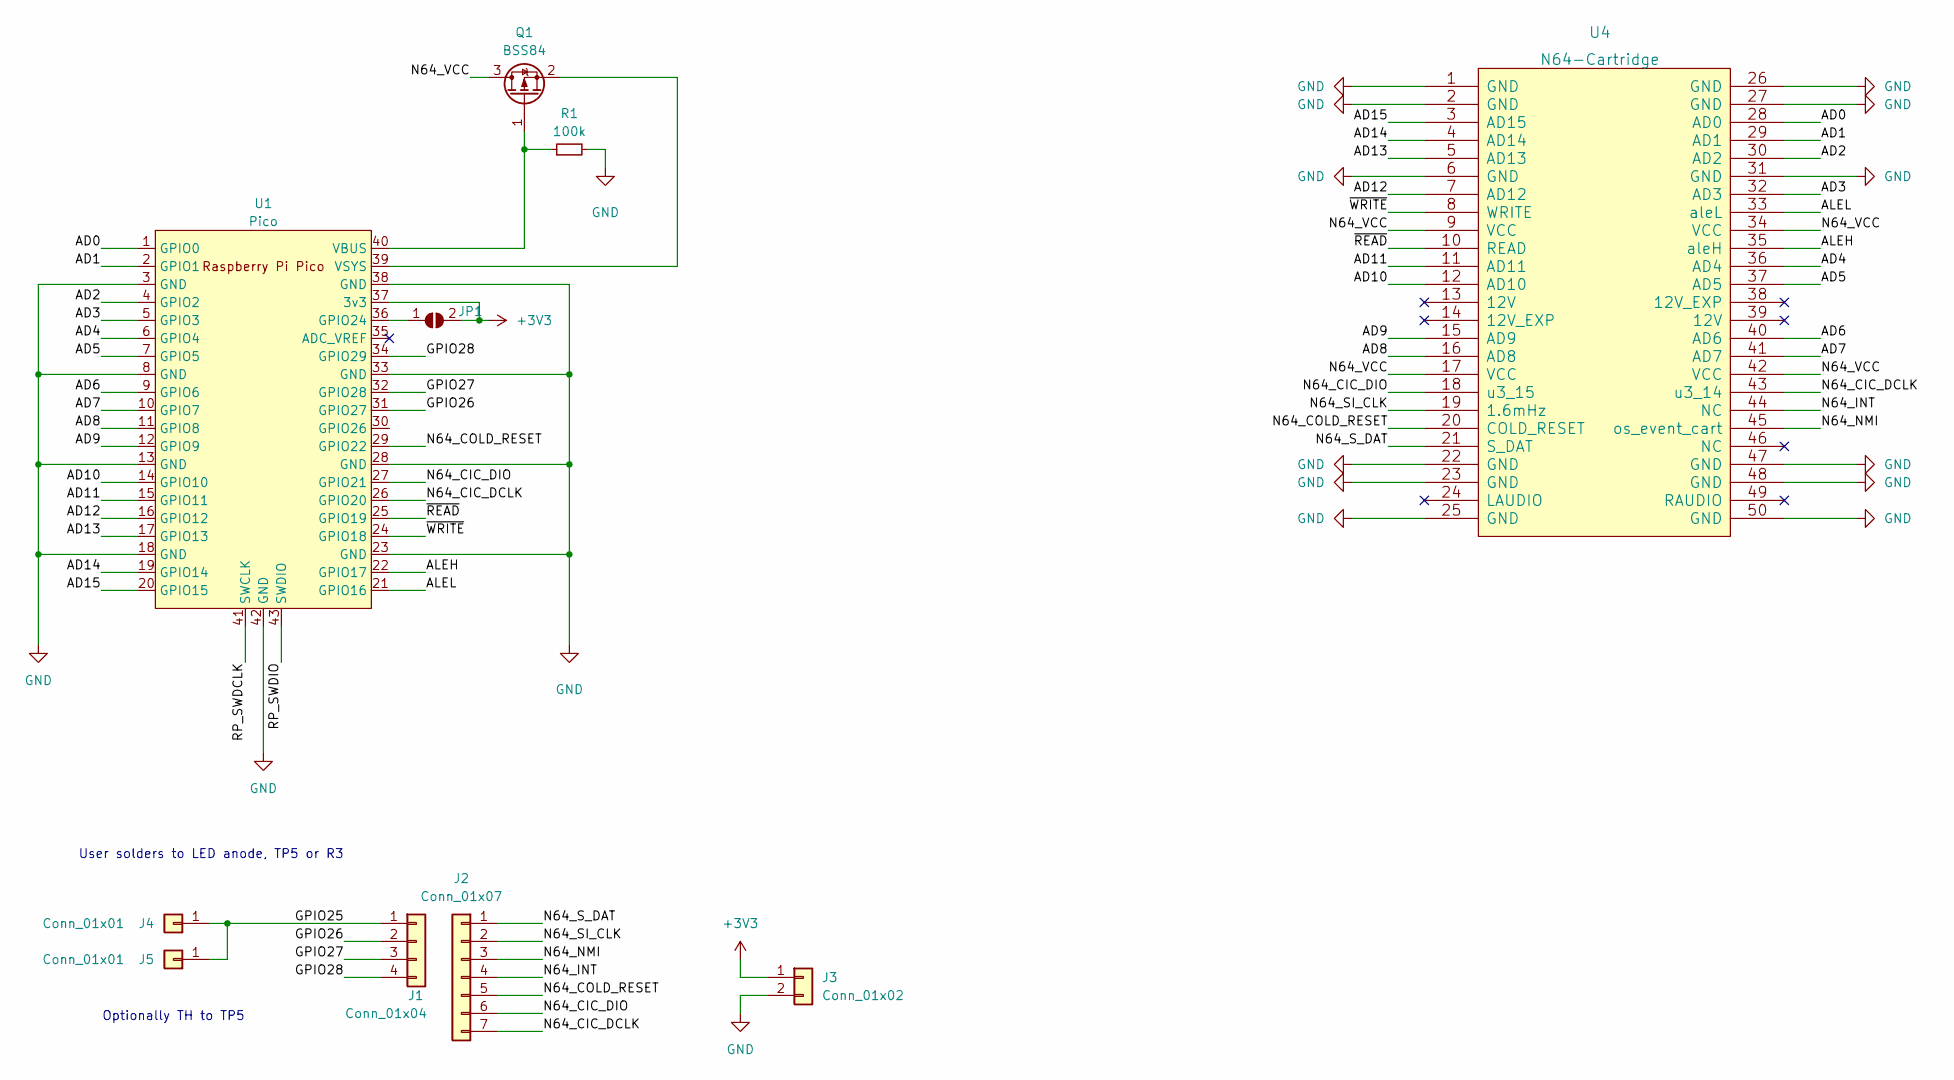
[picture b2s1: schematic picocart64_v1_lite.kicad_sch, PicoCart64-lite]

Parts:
J1: Conn_01x04; PinHeader_1x04_P2.54mm_Vertical
J2: Conn_01x07; PinHeader_1x07_P2.54mm_Vertical
J3: Conn_01x02; PinHeader_1x08_P2.54mm_Vertical
J4, J5: Conn_01x01; PinHeader_1x01_P2.54mm_Vertical
JP1: SolderJumper_2_Open; SolderJumper-2_P1.3mm_Open_RoundedPad1.0x1.5mm
Q1: BSS84; SOT-23
R1: 100k; R_0603_1608Metric_Pad0.98x0.95mm_HandSolder
U1: Pico; RPi_Pico_SMD_TH
U4: N64-Cartridge; N64-Connector

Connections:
+3V3: J3.1, JP1.2 (B), U1.37 (3v3)
/AD0: U1.1 (GPIO0), U4.28 (AD0)
/AD1: U1.2 (GPIO1), U4.29 (AD1)
/AD2: U1.4 (GPIO2), U4.30 (AD2)
/AD3: U1.5 (GPIO3), U4.32 (AD3)
/AD4: U1.6 (GPIO4), U4.36 (AD4)
/AD5: U1.7 (GPIO5), U4.37 (AD5)
/AD6: U1.9 (GPIO6), U4.40 (AD6)
/AD7: U1.10 (GPIO7), U4.41 (AD7)
/AD8: U1.11 (GPIO8), U4.16 (AD8)
/AD9: U1.12 (GPIO9), U4.15 (AD9)
/AD10: U1.14 (GPIO10), U4.12 (AD10)
/AD11: U1.15 (GPIO11), U4.11 (AD11)
/AD12: U1.16 (GPIO12), U4.7 (AD12)
/AD13: U1.17 (GPIO13), U4.5 (AD13)
/AD14: U1.19 (GPIO14), U4.4 (AD14)
/AD15: U1.20 (GPIO15), U4.3 (AD15)
/ALEH: U1.22 (GPIO17), U4.35 (aleH)
/ALEL: U1.21 (GPIO16), U4.33 (aleL)
/GPIO25: J1.1, J4.1, J5.1
/GPIO26: J1.2, U1.31 (GPIO27)
/GPIO27: J1.3, U1.32 (GPIO28)
/GPIO28: J1.4, U1.34 (GPIO29)
/N64_CIC_DCLK: J2.7, U1.26 (GPIO20), U4.43 (u3_14)
/N64_CIC_DIO: J2.6, U1.27 (GPIO21), U4.18 (u3_15)
/N64_COLD_RESET: J2.5, U1.29 (GPIO22), U4.20 (COLD_RESET)
/N64_INT: J2.4, U4.44 (NC)
/N64_NMI: J2.3, U4.45 (os_event_cart)
/N64_SI_CLK: J2.2, U4.19 (1.6mHz)
/N64_S_DAT: J2.1, U4.21 (S_DAT)
/N64_VCC: Q1.3 (D), U4.9 (VCC), U4.17 (VCC), U4.34 (VCC), U4.42 (VCC)
/RP_SWDCLK: U1.41 (SWCLK)
/RP_SWDIO: U1.43 (SWDIO)
/~READ: U1.25 (GPIO19), U4.10 (READ)
/~WRITE: U1.24 (GPIO18), U4.8 (WRITE)
GND: J3.2, R1.2, U1.3 (GND), U1.8 (GND), U1.13 (GND), U1.18 (GND), U1.23 (GND), U1.28 (GND), U1.33 (GND), U1.38 (GND), U1.42 (GND), U4.1 (GND), U4.2 (GND), U4.6 (GND), U4.22 (GND), U4.23 (GND), U4.25 (GND), U4.26 (GND), U4.27 (GND), U4.31 (GND), U4.47 (GND), U4.48 (GND), U4.50 (GND)
unnamed: Q1.1 (G), R1.1, U1.40 (VBUS)
unnamed: Q1.2 (S), U1.39 (VSYS)
unnamed: JP1.1 (A), U1.36 (GPIO24)

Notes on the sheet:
User solders to LED anode, TP5 or R3
Optionally TH to TP5

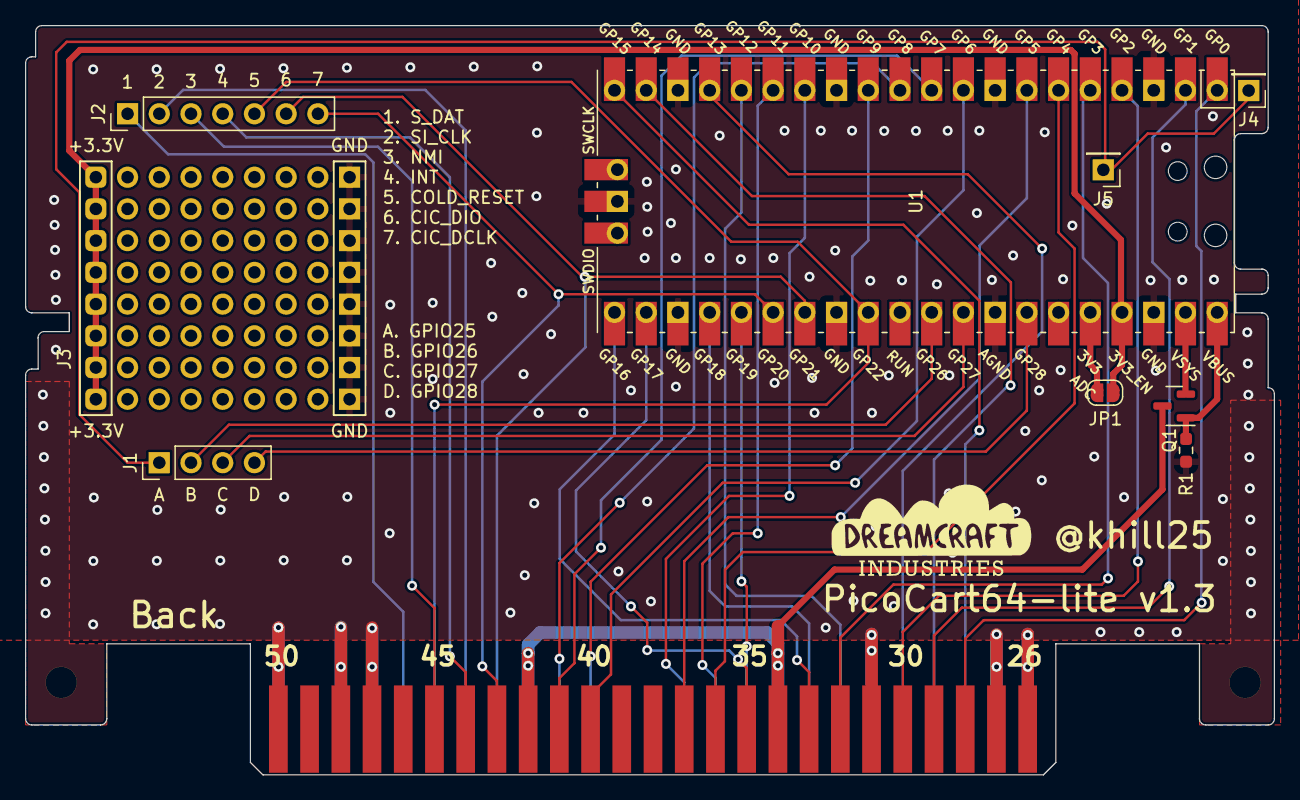
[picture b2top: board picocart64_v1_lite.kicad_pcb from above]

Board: 2 copper layers, 100.0 x 60.0 mm, 10 parts (1 on the bottom side), 37 nets.
